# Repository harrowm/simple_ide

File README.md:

# simple_ide
A very simple IDE interface for the rosco_m68k using two atf22v10 GAL chips

With a lot of thanks to the following projects:  
https://github.com/crmaykish/mackerel-68k/tree/master  
https://github.com/markrvmurray/rosco-ide-ata  

Status as at 11th Feb 2025: This board is not yet working .. the first version has a timing issue on reads.  Working to fix this ..  

To build the rosco firmware with ATA enabled:

    cd
    git clone https://github.com/rosco-m68k/rosco_m68k.git
    cd rosco_m68k/code/firmware/rosco_m68k_firmware
    git submodule update --init --recursive
    WITH_ATA=true ATA_DEBUG=true make clean all

    # copy the ROM images to a SD Card named ROSCO32 on a Mac
    cp rosco_m68k.rom /Volumes/ROSCO32 

.. mmm, had to edit the Makefiule to disable the creation of the rom filesystem as adding in the drivers means the default filesystem doesnt fit into the roms :sob:  
.. double mmm, the generated rom file had an odd size that the in system rom programming utility rejects as invalid.  Patch the file to an even size with the command:  
    
    truncate -s%2 rosco_m68k.rom

    # copy the update flash utility and rom images to a SD card named ROSCO32 on a Mac
    cd
    cd rosco_m68k/code/software
    cp updateflash/updateflash.bin /Volumes/ROSCO32

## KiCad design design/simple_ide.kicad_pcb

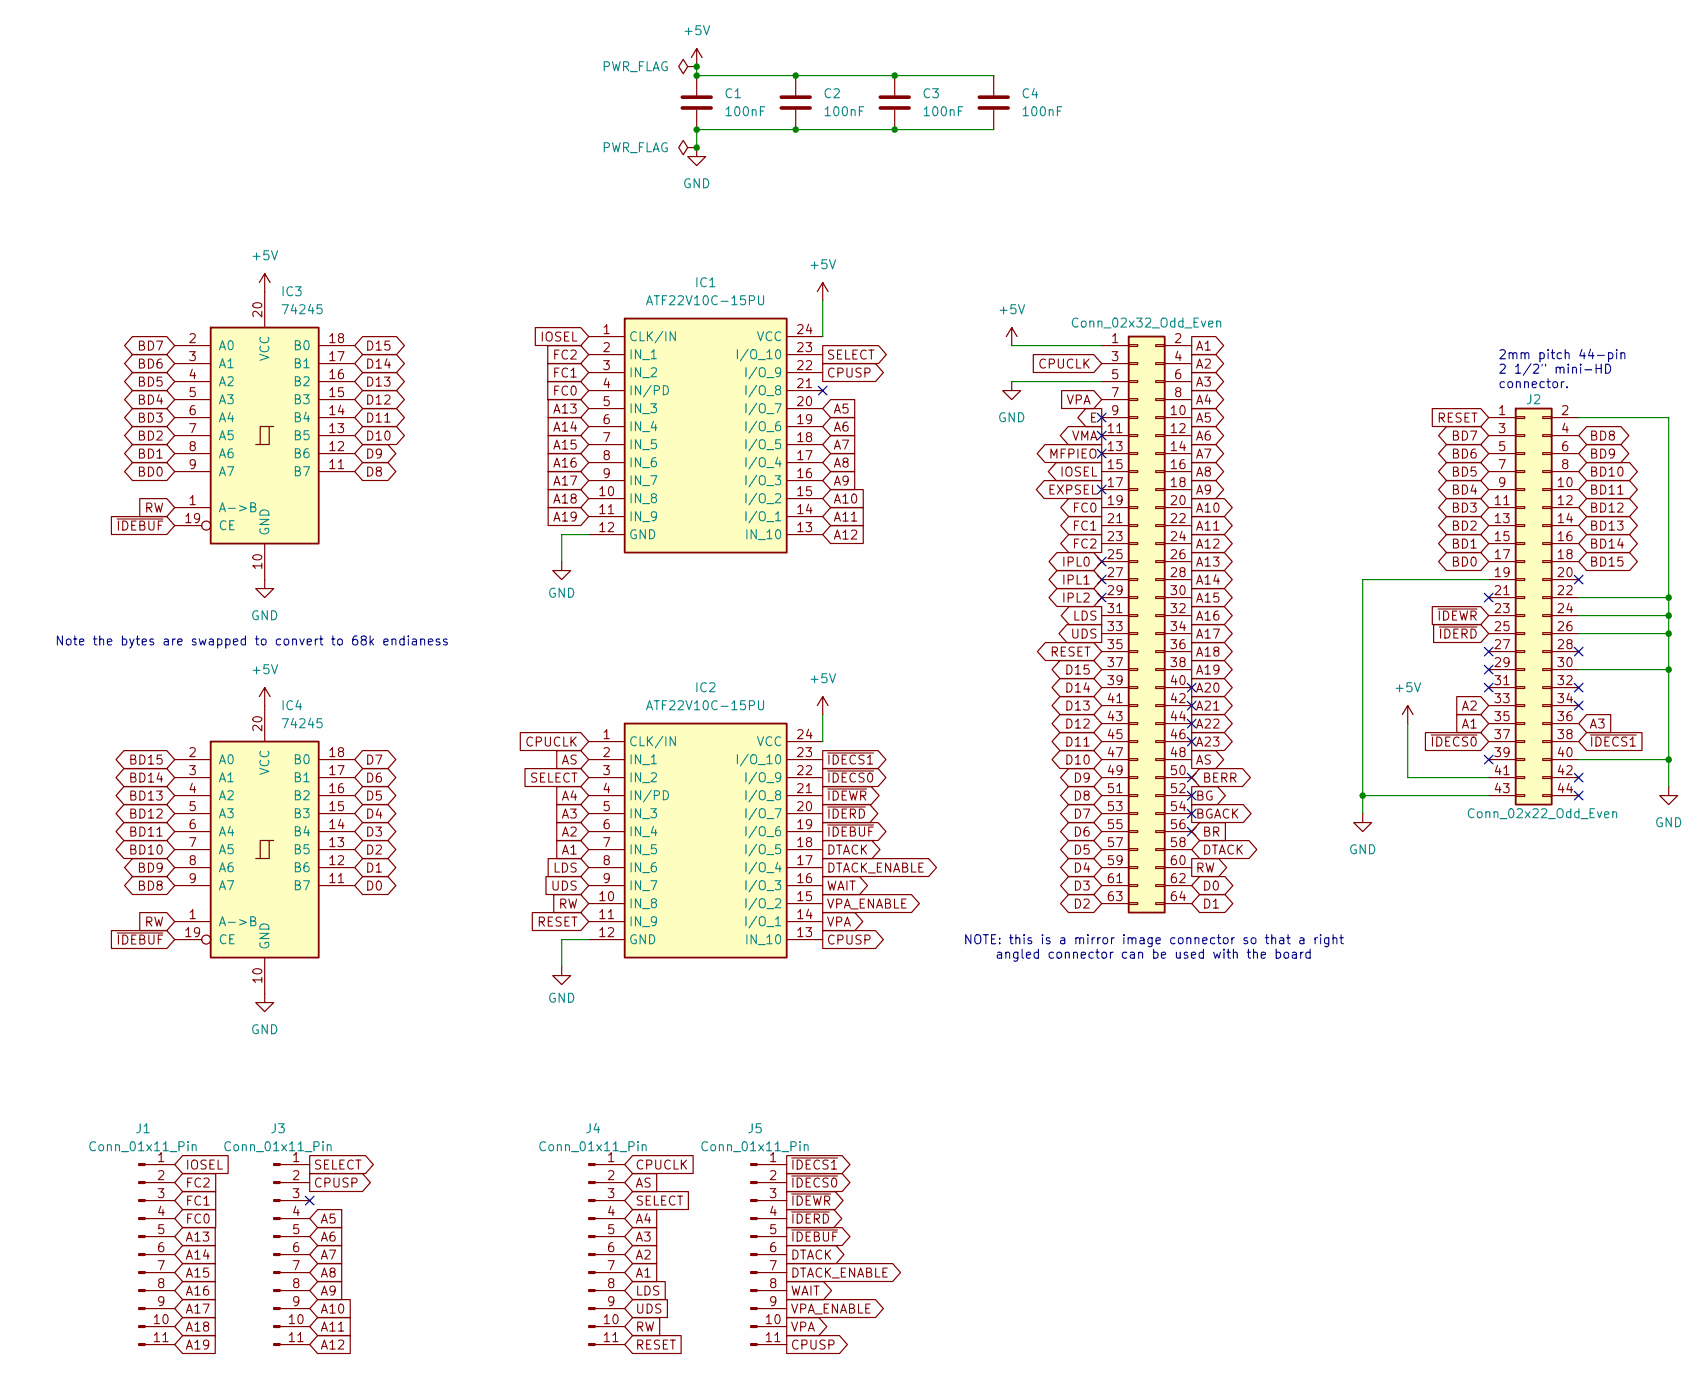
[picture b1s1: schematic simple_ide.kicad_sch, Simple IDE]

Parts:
BUS1: Conn_02x32_Odd_Even; PinHeader_2x32_P2.54mm_Vertical
C1, C2, C3, C4: 100nF; C_Disc_D5.0mm_W2.5mm_P2.50mm; JLC 0805
IC1, IC2: ATF22V10C-15PU; DIP-24_W7.62mm_Socket_LongPads; Mouser Part Number 556-AF22V10C15PU
IC3, IC4: 74245; DIP-20_W7.62mm_LongPads
J1, J3, J4, J5: Conn_01x11_Pin; PinHeader_1x11_P2.54mm_Vertical
J2: Conn_02x22_Odd_Even; PinSocket_2x22_P2.00mm_Vertical

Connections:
+5V: BUS1.1, C1.1, C2.1, C3.1, C4.1, IC1.24 (VCC), IC2.24 (VCC), IC3.20 (VCC), IC4.20 (VCC), J2.41
A1: BUS1.2, IC2.7 (IN_5), J2.35, J4.7
A2: BUS1.4, IC2.6 (IN_4), J2.33, J4.6
A3: BUS1.6, IC2.5 (IN_3), J2.36, J4.5
A4: BUS1.8, IC2.4 (IN/PD), J4.4
A5: BUS1.10, IC1.20 (I/O_7), J3.4
A6: BUS1.12, IC1.19 (I/O_6), J3.5
A7: BUS1.14, IC1.18 (I/O_5), J3.6
A8: BUS1.16, IC1.17 (I/O_4), J3.7
A9: BUS1.18, IC1.16 (I/O_3), J3.8
A10: BUS1.20, IC1.15 (I/O_2), J3.9
A11: BUS1.22, IC1.14 (I/O_1), J3.10
A12: BUS1.24, IC1.13 (IN_10), J3.11
A13: BUS1.26, IC1.5 (IN_3), J1.5
A14: BUS1.28, IC1.6 (IN_4), J1.6
A15: BUS1.30, IC1.7 (IN_5), J1.7
A16: BUS1.32, IC1.8 (IN_6), J1.8
A17: BUS1.34, IC1.9 (IN_7), J1.9
A18: BUS1.36, IC1.10 (IN_8), J1.10
A19: BUS1.38, IC1.11 (IN_9), J1.11
A20: BUS1.40
A21: BUS1.42
A22: BUS1.44
A23: BUS1.46
AS: BUS1.48, IC2.2 (IN_1), J4.2
BD0: IC3.9 (A7), J2.17
BD1: IC3.8 (A6), J2.15
BD2: IC3.7 (A5), J2.13
BD3: IC3.6 (A4), J2.11
BD4: IC3.5 (A3), J2.9
BD5: IC3.4 (A2), J2.7
BD6: IC3.3 (A1), J2.5
BD7: IC3.2 (A0), J2.3
BD8: IC4.9 (A7), J2.4
BD9: IC4.8 (A6), J2.6
BD10: IC4.7 (A5), J2.8
BD11: IC4.6 (A4), J2.10
BD12: IC4.5 (A3), J2.12
BD13: IC4.4 (A2), J2.14
BD14: IC4.3 (A1), J2.16
BD15: IC4.2 (A0), J2.18
BERR: BUS1.50
BG: BUS1.52
BGACK: BUS1.54
BR: BUS1.56
CPUCLK: BUS1.3, IC2.1 (CLK/IN), J4.1
CPUSP: IC1.22 (I/O_9), IC2.13 (IN_10), J3.2, J5.11
D0: BUS1.62, IC4.11 (B7)
D1: BUS1.64, IC4.12 (B6)
D2: BUS1.63, IC4.13 (B5)
D3: BUS1.61, IC4.14 (B4)
D4: BUS1.59, IC4.15 (B3)
D5: BUS1.57, IC4.16 (B2)
D6: BUS1.55, IC4.17 (B1)
D7: BUS1.53, IC4.18 (B0)
D8: BUS1.51, IC3.11 (B7)
D9: BUS1.49, IC3.12 (B6)
D10: BUS1.47, IC3.13 (B5)
D11: BUS1.45, IC3.14 (B4)
D12: BUS1.43, IC3.15 (B3)
D13: BUS1.41, IC3.16 (B2)
D14: BUS1.39, IC3.17 (B1)
D15: BUS1.37, IC3.18 (B0)
DTACK: BUS1.58, IC2.18 (I/O_5), J5.6
DTACK_ENABLE: IC2.17 (I/O_4), J5.7
E: BUS1.9
EXPSEL: BUS1.17
FC0: BUS1.19, IC1.4 (IN/PD), J1.4
FC1: BUS1.21, IC1.3 (IN_2), J1.3
FC2: BUS1.23, IC1.2 (IN_1), J1.2
GND: BUS1.5, C1.2, C2.2, C3.2, C4.2, IC1.12 (GND), IC2.12 (GND), IC3.10 (GND), IC4.10 (GND), J2.2, J2.19, J2.22, J2.24, J2.26, J2.30, J2.40, J2.43
IOSEL: BUS1.15, IC1.1 (CLK/IN), J1.1
IPL0: BUS1.25
IPL1: BUS1.27
IPL2: BUS1.29
LDS: BUS1.31, IC2.8 (IN_6), J4.8
MFPIEO: BUS1.13
RESET: BUS1.35, IC2.11 (IN_9), J2.1, J4.11
RW: BUS1.60, IC2.10 (IN_8), IC3.1 (A->B), IC4.1 (A->B), J4.10
SELECT: IC1.23 (I/O_10), IC2.3 (IN_2), J3.1, J4.3
UDS: BUS1.33, IC2.9 (IN_7), J4.9
VMA: BUS1.11
VPA: BUS1.7, IC2.14 (I/O_1), J5.10
VPA_ENABLE: IC2.15 (I/O_2), J5.9
WAIT: IC2.16 (I/O_3), J5.8
~IDEBUF: IC2.19 (I/O_6), IC3.19 (CE), IC4.19 (CE), J5.5
~IDECS0: IC2.22 (I/O_9), J2.37, J5.2
~IDECS1: IC2.23 (I/O_10), J2.38, J5.1
~IDERD: IC2.20 (I/O_7), J2.25, J5.4
~IDEWR: IC2.21 (I/O_8), J2.23, J5.3

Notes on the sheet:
2mm pitch 44-pin 2 1/2" mini-HD connector.
NOTE: this is a mirror image connector so that a right angled connector can be used with the board
Note the bytes are swapped to convert to 68k endianess

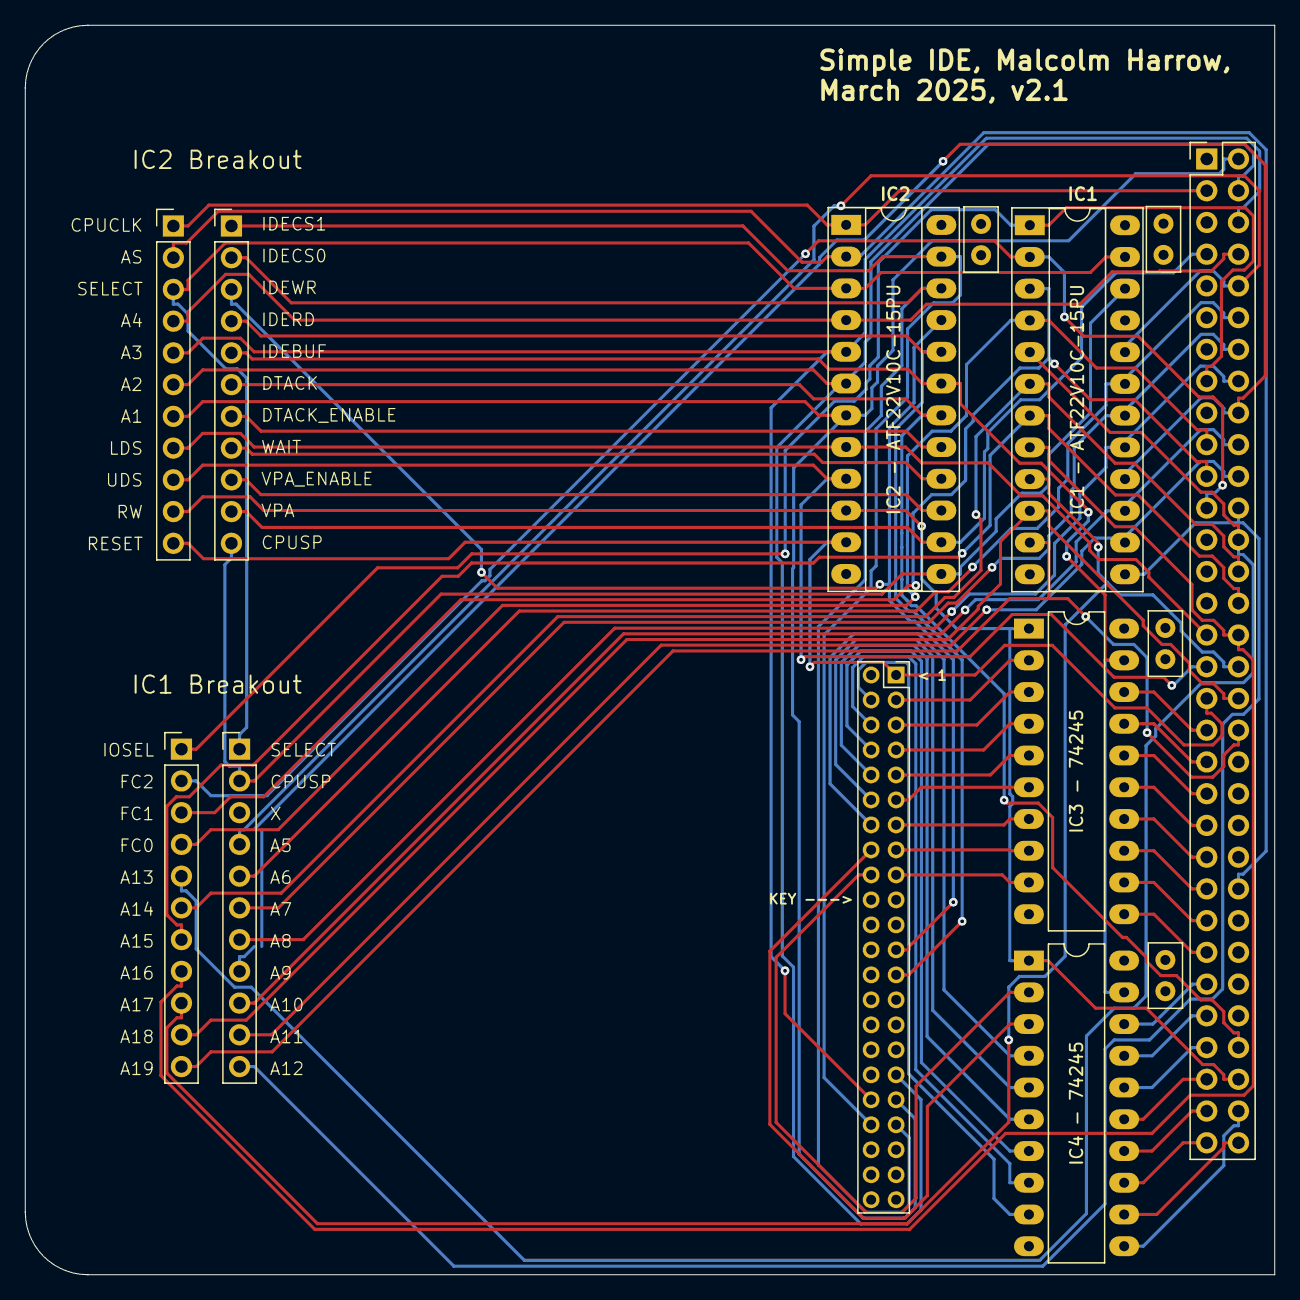
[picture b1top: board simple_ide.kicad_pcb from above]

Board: 4 copper layers, 100.0 x 100.0 mm, 14 parts (0 on the bottom side), 75 nets.

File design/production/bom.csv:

Designator,Footprint,Quantity,Value,LCSC Part #
BUS1,PinHeader_2x32_P2.54mm_Vertical,1,Conn_02x32_Odd_Even,
"C1, C2, C3, C4",C_Disc_D5.0mm_W2.5mm_P2.50mm,4,100nF,C49678
"IC1, IC2",DIP-24_W7.62mm_Socket_LongPads,2,ATF22V10C-15PU,
"IC3, IC4",DIP-20_W7.62mm_LongPads,2,74245,
"J1, J3, J4, J5",PinHeader_1x11_P2.54mm_Vertical,4,Conn_01x11_Pin,
J2,PinSocket_2x22_P2.00mm_Vertical,1,Conn_02x22_Odd_Even,

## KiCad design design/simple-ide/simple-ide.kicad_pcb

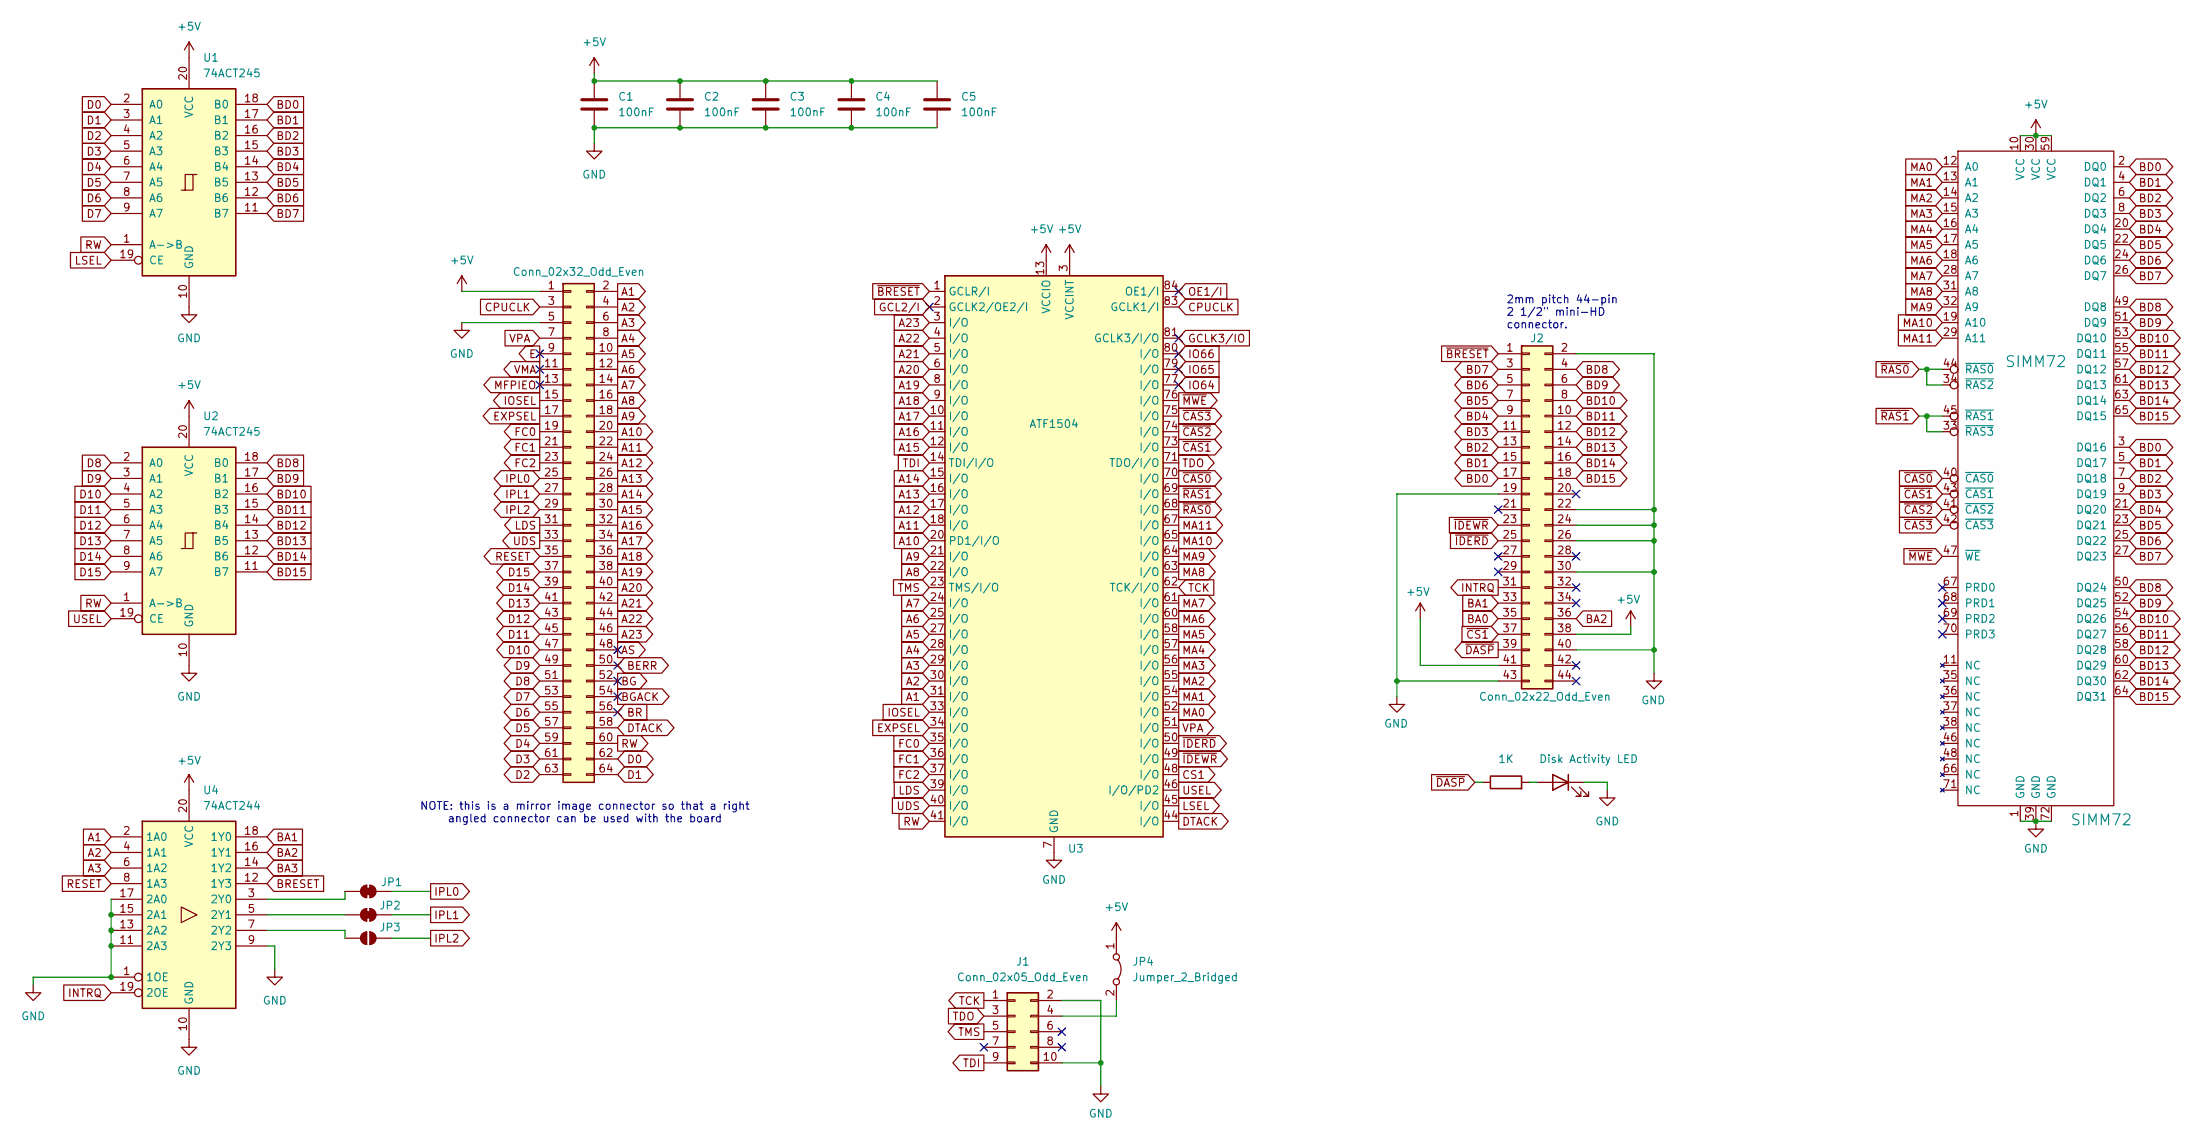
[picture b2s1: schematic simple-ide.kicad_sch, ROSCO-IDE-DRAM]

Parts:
BUS1: Conn_02x32_Odd_Even; PinHeader_2x32_P2.54mm_Vertical
C1, C2, C3, C4, C5: 100nF; C_0805_2012Metric_Pad1.18x1.45mm_HandSolder; JLC 0805
D1: Disk Activity LED; LED_0805_2012Metric_Pad1.15x1.40mm_HandSolder; LCSC C2297
J1: Conn_02x05_Odd_Even; IDC-Header_2x05_P2.54mm_Vertical
J2: Conn_02x22_Odd_Even; PinSocket_2x22_P2.00mm_Vertical
JP1, JP2: SolderJumper_2_Bridged; SolderJumper-2_P1.3mm_Bridged_RoundedPad1.0x1.5mm
JP3: SolderJumper_2_Open; SolderJumper-2_P1.3mm_Open_RoundedPad1.0x1.5mm
JP4: Jumper_2_Bridged; PinHeader_1x02_P2.54mm_Vertical
R1: 1K; R_0805_2012Metric_Pad1.20x1.40mm_HandSolder; JLC 805
SIMM72: SIMM72
U1, U2: 74ACT245; SOIC-20W_7.5x12.8mm_P1.27mm
U3: ATF1504; PLCC-84_THT-Socket
U4: 74ACT244; SOIC-20W_7.5x12.8mm_P1.27mm

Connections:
A1: BUS1.2, U3.31 (I/O), U4.2 (1A0)
A2: BUS1.4, U3.30 (I/O), U4.4 (1A1)
A3: BUS1.6, U3.29 (I/O), U4.6 (1A2)
A4: BUS1.8, U3.28 (I/O)
A5: BUS1.10, U3.27 (I/O)
A6: BUS1.12, U3.25 (I/O)
A7: BUS1.14, U3.24 (I/O)
A8: BUS1.16, U3.22 (I/O)
A9: BUS1.18, U3.21 (I/O)
A10: BUS1.20, U3.20 (PD1/I/O)
A11: BUS1.22, U3.18 (I/O)
A12: BUS1.24, U3.17 (I/O)
A13: BUS1.26, U3.16 (I/O)
A14: BUS1.28, U3.15 (I/O)
A15: BUS1.30, U3.12 (I/O)
A16: BUS1.32, U3.11 (I/O)
A17: BUS1.34, U3.10 (I/O)
A18: BUS1.36, U3.9 (I/O)
A19: BUS1.38, U3.8 (I/O)
A20: BUS1.40, U3.6 (I/O)
A21: BUS1.42, U3.5 (I/O)
A22: BUS1.44, U3.4 (I/O)
AS: BUS1.48
BA0: J2.35
BA1: J2.33, U4.18 (1Y0)
BA2: J2.36, U4.16 (1Y1)
BA3: U4.14 (1Y2)
BD0: J2.17, SIMM72.2 (DQ0), SIMM72.3 (DQ16), U1.18 (B0)
BD1: J2.15, SIMM72.4 (DQ1), SIMM72.5 (DQ17), U1.17 (B1)
BD2: J2.13, SIMM72.6 (DQ2), SIMM72.7 (DQ18), U1.16 (B2)
BD3: J2.11, SIMM72.8 (DQ3), SIMM72.9 (DQ19), U1.15 (B3)
BD4: J2.9, SIMM72.20 (DQ4), SIMM72.21 (DQ20), U1.14 (B4)
BD5: J2.7, SIMM72.22 (DQ5), SIMM72.23 (DQ21), U1.13 (B5)
BD6: J2.5, SIMM72.24 (DQ6), SIMM72.25 (DQ22), U1.12 (B6)
BD7: J2.3, SIMM72.26 (DQ7), SIMM72.27 (DQ23), U1.11 (B7)
BD8: J2.4, SIMM72.49 (DQ8), SIMM72.50 (DQ24), U2.18 (B0)
BD9: J2.6, SIMM72.51 (DQ9), SIMM72.52 (DQ25), U2.17 (B1)
BD10: J2.8, SIMM72.53 (DQ10), SIMM72.54 (DQ26), U2.16 (B2)
BD11: J2.10, SIMM72.55 (DQ11), SIMM72.56 (DQ27), U2.15 (B3)
BD12: J2.12, SIMM72.57 (DQ12), SIMM72.58 (DQ28), U2.14 (B4)
BD13: J2.14, SIMM72.60 (DQ29), SIMM72.61 (DQ13), U2.13 (B5)
BD14: J2.16, SIMM72.62 (DQ30), SIMM72.63 (DQ14), U2.12 (B6)
BD15: J2.18, SIMM72.64 (DQ31), SIMM72.65 (DQ15), U2.11 (B7)
BERR: BUS1.50
BG: BUS1.52
BGACK: BUS1.54
BR: BUS1.56
BRESET: U4.12 (1Y3)
CPUCLK: BUS1.3, U3.83 (GCLK1/I)
CS1: U3.48 (I/O)
D0: BUS1.62, U1.2 (A0)
D1: BUS1.64, U1.3 (A1)
D2: BUS1.63, U1.4 (A2)
D3: BUS1.61, U1.5 (A3)
D4: BUS1.59, U1.6 (A4)
D5: BUS1.57, U1.7 (A5)
D6: BUS1.55, U1.8 (A6)
D7: BUS1.53, U1.9 (A7)
D8: BUS1.51, U2.2 (A0)
D9: BUS1.49, U2.3 (A1)
D10: BUS1.47, U2.4 (A2)
D11: BUS1.45, U2.5 (A3)
D12: BUS1.43, U2.6 (A4)
D13: BUS1.41, U2.7 (A5)
D14: BUS1.39, U2.8 (A6)
D15: BUS1.37, U2.9 (A7)
DTACK: BUS1.58, U3.44 (I/O)
E: BUS1.9
EXPSEL: BUS1.17, U3.34 (I/O)
FC0: BUS1.19, U3.35 (I/O)
FC1: BUS1.21, U3.36 (I/O)
FC2: BUS1.23, U3.37 (I/O)
GCL2/I: U3.2 (GCLK2/OE2/I)
GCLK3/IO: U3.81 (GCLK3/I/O)
GND: BUS1.5, C1.2, C2.2, C3.2, C4.2, C5.2, D1.1 (K), J1.2, J1.10, J2.2, J2.19, J2.22, J2.24, J2.26, J2.30, J2.40, J2.43, SIMM72.1 (GND), SIMM72.39 (GND), SIMM72.72 (GND), U1.10 (GND), U2.10 (GND), U3.7 (GND), U3.19 (GND), U3.32 (GND), U3.42 (GND), U3.47 (GND), U3.59 (GND), U3.72 (GND), U3.82 (GND), U4.1 (1OE), U4.9 (2Y3), U4.10 (GND), U4.11 (2A3), U4.13 (2A2), U4.15 (2A1), U4.17 (2A0)
INTRQ: J2.31, U4.19 (2OE)
IO64: U3.77 (I/O)
IO65: U3.79 (I/O)
IO66: U3.80 (I/O)
IOSEL: BUS1.15, U3.33 (I/O)
IPL0: BUS1.25, JP1.2 (B)
IPL1: BUS1.27, JP2.2 (B)
IPL2: BUS1.29, JP3.2 (B)
LDS: BUS1.31, U3.39 (I/O)
LSEL: U1.19 (CE), U3.45 (I/O)
MA0: SIMM72.12 (A0), U3.52 (I/O)
MA1: SIMM72.13 (A1), U3.54 (I/O)
MA2: SIMM72.14 (A2), U3.55 (I/O)
MA3: SIMM72.15 (A3), U3.56 (I/O)
MA4: SIMM72.16 (A4), U3.57 (I/O)
MA5: SIMM72.17 (A5), U3.58 (I/O)
MA6: SIMM72.18 (A6), U3.60 (I/O)
MA7: SIMM72.28 (A7), U3.61 (I/O)
MA8: SIMM72.31 (A8), U3.63 (I/O)
MA9: SIMM72.32 (A9), U3.64 (I/O)
MA10: SIMM72.19 (A10), U3.65 (I/O)
MA11: SIMM72.29 (A11), U3.67 (I/O)
MFPIEO: BUS1.13
unnamed: D1.2 (A), R1.2
unnamed: J1.4, JP4.2 (B)
unnamed: JP1.1 (A), U4.3 (2Y0)
unnamed: JP2.1 (A), U4.5 (2Y1)
unnamed: JP3.1 (A), U4.7 (2Y2)
OE1/I: U3.84 (OE1/I)
RESET: BUS1.35, U4.8 (1A3)
RW: BUS1.60, U1.1 (A->B), U2.1 (A->B), U3.41 (I/O)
TCK: J1.1, U3.62 (TCK/I/O)
TDI: J1.9, U3.14 (TDI/I/O)
TDO: J1.3, U3.71 (TDO/I/O)
TMS: J1.5, U3.23 (TMS/I/O)
UDS: BUS1.33, U3.40 (I/O)
USEL: U2.19 (CE), U3.46 (I/O/PD2)
VMA: BUS1.11
VPA: BUS1.7, U3.51 (I/O)
~BRESET: J2.1, U3.1 (GCLR/I)
~CAS0: SIMM72.40 (~CAS0), U3.70 (I/O)
~CAS1: SIMM72.43 (~CAS1), U3.73 (I/O)
~CAS2: SIMM72.41 (~CAS2), U3.74 (I/O)
~CAS3: SIMM72.42 (~CAS3), U3.75 (I/O)
~CS1: J2.37
~DASP: J2.39, R1.1
~IDERD: J2.25, U3.50 (I/O)
~IDEWR: J2.23, U3.49 (I/O)
~MWE: SIMM72.47 (~WE), U3.76 (I/O)
~RAS0: SIMM72.34 (~RAS2), SIMM72.44 (~RAS0), U3.68 (I/O)
~RAS1: SIMM72.33 (~RAS3), SIMM72.45 (~RAS1), U3.69 (I/O)

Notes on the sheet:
2mm pitch 44-pin 2 1/2" mini-HD connector.
NOTE: this is a mirror image connector so that a right angled connector can be used with the board

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
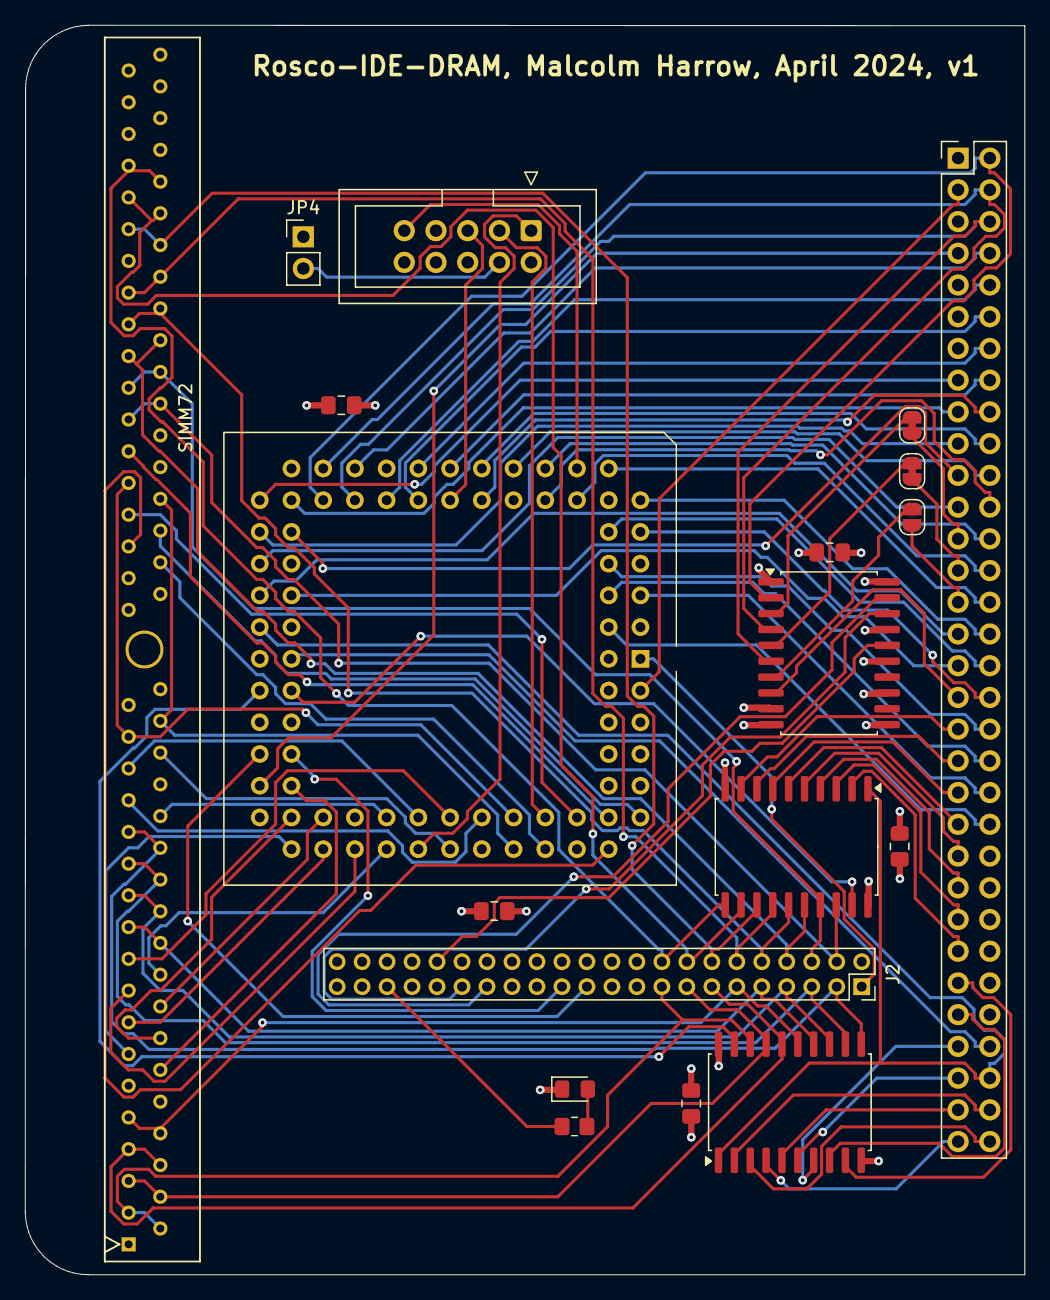
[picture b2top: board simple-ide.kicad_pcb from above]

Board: 4 copper layers, 80.0 x 100.0 mm, 19 parts (0 on the bottom side), 108 nets.

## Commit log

2024-11-04 get pld working
2024-11-04 Get pld code working
2025-01-08 Simplify WinCUPL
2025-01-14 Added KiCad design
2025-01-15 Recheck WinCUPL against design
2025-01-16 Compile Wincuple and reroute pins to ensure outputs on output pins
2025-01-16 Add production files
2025-02-02 IC1 working (I think ..), now onto IC2
2025-02-04 Add release v1
2025-02-04 Start work on v2
2025-02-10 Add in script to contriol WinCupl
2025-02-10 Update Makefile
2025-02-10 Add in old ic2 version
2025-02-10 Remove old ic2 version
2025-02-11 Further work on pld, tidy up readme, add images
2025-02-11 Tidy up readme
2025-03-07 First test of v2 production files .. seems to read a disk ok
2025-03-07 First successful reading of a disk
2025-03-14 Move to F200040
2025-03-18 Save copy of firmware

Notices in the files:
design/simple-ide/simple-ide.kicad_sch:
Malcolm Harrow, MIT license, from work by Mark Murray
